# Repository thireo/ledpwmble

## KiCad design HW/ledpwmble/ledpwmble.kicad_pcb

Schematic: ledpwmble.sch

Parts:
C1, C2: 15pF; C_0603_1608Metric
C3, C5, C8: 100nF; C_0603_1608Metric
C4: 10uF; C_0603_1608Metric
C6, C7: 22uF; C_0603_1608Metric
D1, D2, D3: LED_ALT; TestPoint_2Pads_Pitch2.54mm_Drill0.8mm
FL1: ACP3225
IC1: ATSAMD21G18A-AU; TQFP-48_7x7mm_P0.5mm
J1: Conn_01x08; PinSocket_1x08_P2.54mm_Vertical
L2: 2.2uH; L_Wuerth_MAPI-3020
Q1, Q2, Q3: NTR5103NT1G; SOT-23
R1: 100k; R_0603_1608Metric
R2, R3, R4: 1k; R_0603_1608Metric
TP1: PSU+; TestPoint_Plated_Hole_D3.0mm
TP2: PSU-; TestPoint_Plated_Hole_D3.0mm
U1: MIC5504-3.3YM5; SOT-23-5
U2: TPS62173DSG; WSON-8-1EP_2x2mm_P0.5mm_EP0.9x1.6mm_ThermalVias
Y1: Crystal_Small; Crystal_SMD_3215-2Pin_3.2x1.5mm

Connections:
+5V: C3.1, C7.1, C8.1, L2.2, R1.1, U1.1 (VIN), U1.3 (EN), U2.6 (VOS)
+12V: C5.1, C6.1, D1.2 (A), D2.2 (A), D3.2 (A), FL1.4, U2.2 (VIN), U2.3 (EN)
/BLE_RX: IC1.15 (PA10), J1.4
/BLE_TX: IC1.13 (PA08), J1.3
/DEBUG/MCU_RESET: IC1.40 (RESETN); also elsewhere on the board
/DEBUG/SWCLK: IC1.45 (PA30); also elsewhere on the board
/DEBUG/SWDIO: IC1.46 (PA31); also elsewhere on the board
/PWM_0-TCC2: IC1.21 (PA12), R3.2
/PWM_1-TCC0: IC1.23 (PA14), R4.2
/PWM_2-TCC5: IC1.20 (PB11), R2.2
/SAMD21PWR/GNDANA: IC1.5 (GNDANA); also elsewhere on the board
/SAMD21PWR/VDDANA: IC1.6 (VDDANA); also elsewhere on the board
/SAMD21PWR/VDDCORE: IC1.43 (VDDCORE); also elsewhere on the board
/UART_TX: IC1.47 (PB02); also elsewhere on the board
GND: C1.2, C2.2, C5.2, C6.2, FL1.3, IC1.18 (GND), IC1.35 (GND), IC1.42 (GND), J1.2, J1.7, Q1.2 (S), Q2.2 (S), Q3.2 (S), U2.1 (PGND), U2.4 (AGND), U2.9 (PAD); also elsewhere on the board
unnamed: C1.1, IC1.2 (PA01), Y1.2
unnamed: C2.1, IC1.1 (PA00), Y1.1
unnamed: C3.2, C4.2, U1.2 (GND)
unnamed: C7.2, C8.2, U2.5 (FB)
unnamed: D1.1 (K), Q1.3 (D)
unnamed: D2.1 (K), Q2.3 (D)
unnamed: D3.1 (K), Q3.3 (D)
unnamed: FL1.1, TP1.1
unnamed: FL1.2, TP2.1
unnamed: L2.1, U2.7 (SW)
unnamed: Q1.1 (G), R2.1
unnamed: Q2.1 (G), R3.1
unnamed: Q3.1 (G), R4.1
unnamed: R1.2, U2.8 (PG)
VCC: C4.1, IC1.17 (VDDIO), IC1.36 (VDDIO), IC1.44 (VDDIN), J1.5, U1.5 (VOUT); also elsewhere on the board

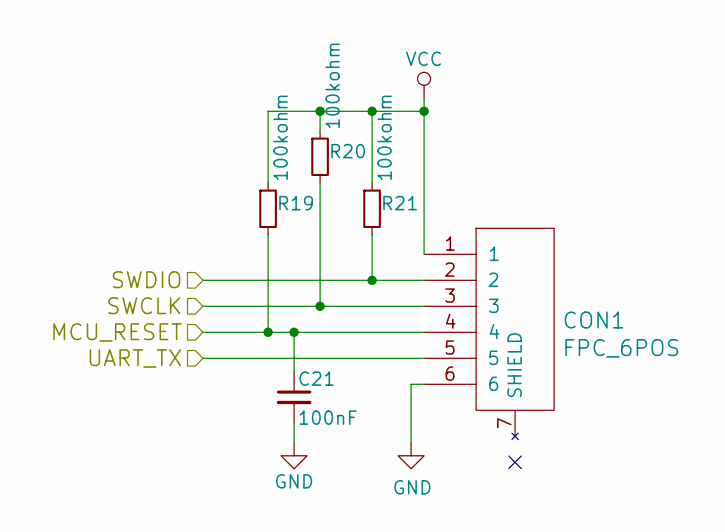
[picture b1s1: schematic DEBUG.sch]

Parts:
C21: 100nF; C_0603_1608Metric
CON1: FPC_6POS; HFW6R_2STE1LF
R19, R20, R21: 100kohm; R_0603_1608Metric

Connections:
/DEBUG/MCU_RESET: C21.1, CON1.4, R19.2; also elsewhere on the board
/DEBUG/SWCLK: CON1.3, R20.2; also elsewhere on the board
/DEBUG/SWDIO: CON1.2, R21.2; also elsewhere on the board
/UART_TX: CON1.5; also elsewhere on the board
GND: C21.2, CON1.6; also elsewhere on the board
VCC: CON1.1, R19.1, R20.1, R21.1; also elsewhere on the board

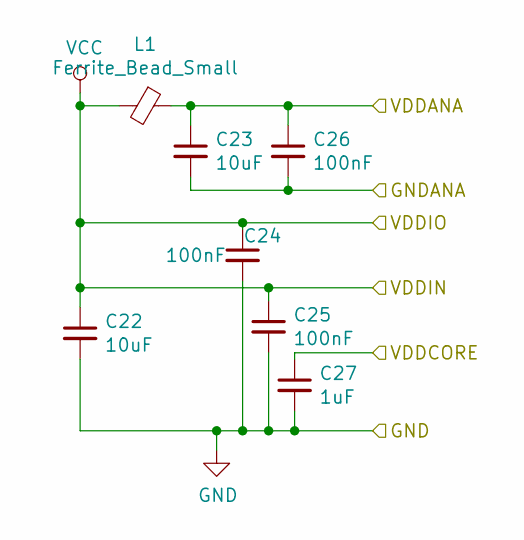
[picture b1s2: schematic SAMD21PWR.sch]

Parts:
C22, C23: 10uF; C_0805_HandSoldering
C24, C25, C26: 100nF; C_0805_HandSoldering
C27: 1uF; C_0805_HandSoldering
L1: Ferrite_Bead_Small; C_0603_HandSoldering

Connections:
/SAMD21PWR/GNDANA: C23.2, C26.2; also elsewhere on the board
/SAMD21PWR/VDDANA: C23.1, C26.1, L1.1; also elsewhere on the board
/SAMD21PWR/VDDCORE: C27.1; also elsewhere on the board
GND: C22.2, C24.2, C25.2, C27.2; also elsewhere on the board
VCC: C22.1, C24.1, C25.1, L1.2; also elsewhere on the board

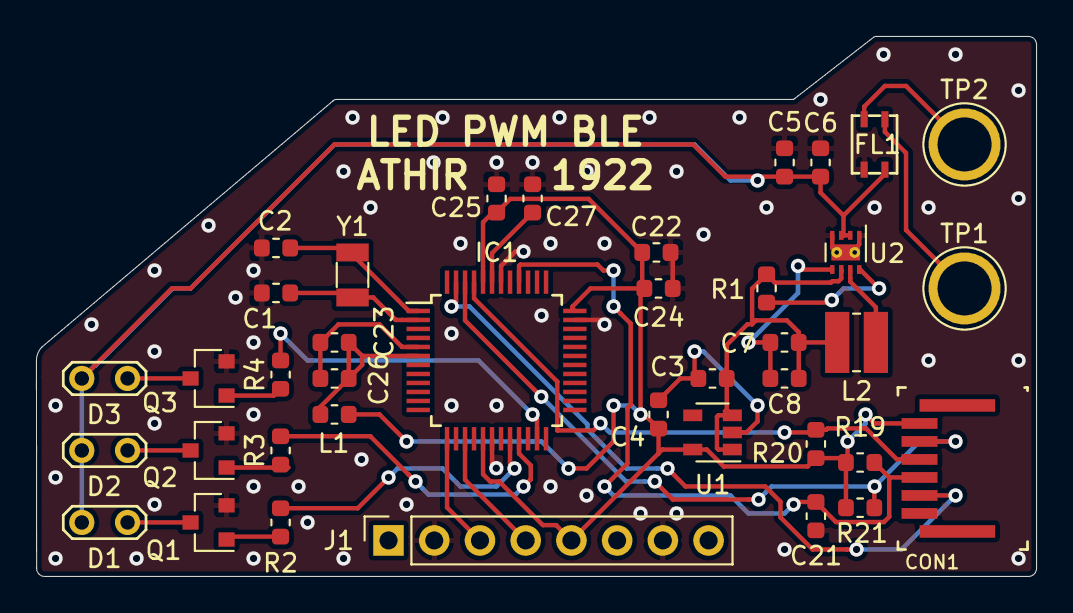
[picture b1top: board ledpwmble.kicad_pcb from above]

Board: 2 copper layers, 55.6 x 30.0 mm, 39 parts (0 on the bottom side), 30 nets.

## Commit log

2019-06-01 Initial HW pcb commit
2019-06-06 HW: Rev 1 - 1922
2019-06-15 SW: initial commit
2020-08-21 Sorry?
